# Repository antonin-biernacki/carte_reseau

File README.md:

# Carte réseau USB à base d'ATmega

Carte réseau USB conçue sous **KiCad**, construite autour d'un **ATmega**. Elle se présente comme une interface Ethernet (classe **RNDIS**, via la bibliothèque LUFA) et doit permettre à une carte mère de lire, écrire et lister des fichiers sur un PC, grâce à un protocole maison transporté en UDP : le **ProtocolAntique**. Un serveur C côté PC traite les requêtes.

> **État du projet** : ce dépôt est un état d'avancement. Le projet n'a pas été mené à son terme, voir [Avancement](#avancement).

## Sommaire

- [Contexte](#contexte)
- [Avancement](#avancement)
- [Aperçu](#aperçu)
- [Fonctionnalités](#fonctionnalités)
- [Structure du projet](#structure-du-projet)
- [Matériel](#matériel)
- [Compilation et téléversement](#compilation-et-téléversement)
- [Utilisation](#utilisation)
- [Fonctionnement interne](#fonctionnement-interne)
- [Crédits](#crédits)

## Contexte

L'idée est la suivante :

1. la carte mère exprime un besoin (`ls`, `read`, `write`) à la carte réseau ;
2. la carte réseau encapsule ce besoin dans une requête UDP (ProtocolAntique) et l'envoie au PC par l'USB ;
3. un serveur tourne sur le PC, exécute l'opération sur son système de fichiers et répond.

## Avancement

| Élément                                                             | État      |
|---------------------------------------------------------------------|-----------|
| Schématique et routage de la carte, soudage                         | Terminé   |
| Programmation de la carte et pilotage des LEDs                      | Terminé   |
| Reconnaissance de la carte comme interface réseau USB (RNDIS), `ping` | Terminé   |
| Réception de trames Ethernet et de paquets UDP (signalée par LED)   | Terminé   |
| Envoi d'une trame UDP depuis la carte (capturée avec Wireshark)     | Terminé   |
| Spécification du ProtocolAntique                                    | Terminé   |
| Serveur PC (`ls`, `read`, `write`) et ses outils de test            | Terminé et testé |
| Traitement des requêtes ProtocolAntique par la carte                | À faire   |
| Liaison avec la carte mère (shield), par SPI                        | À faire   |

Faute de temps, la carte n'a pas été reliée à la carte mère. La communication SPI a toutefois été validée lors du développement de l'ordonnanceur.

## Aperçu

### Schématique

### Routage

## Fonctionnalités

- Énumération USB de la carte comme interface Ethernet (RNDIS)
- Réception et traitement de trames Ethernet, avec indication par LED
- Envoi d'une trame UDP de test contenant une requête ProtocolAntique
- Protocole applicatif maison (ProtocolAntique) à trois opérations : `LS`, `READ`, `WRITE`
- Serveur PC UDP qui exécute ces opérations sur le système de fichiers
- Outils de simulation pour tester le serveur sans la carte (client de requêtes et faux récepteur)

## Structure du projet

```text
.
├── docs/                              # Captures et vidéos de démonstration
├── hardware/                          # Projet KiCad de la carte réseau
└── software/
    ├── CReseau/
    │   ├── test.c                     # Test autonome des LEDs de la carte
    │   └── Makefile
    ├── lufa-LUFA-210130-NSI/
    │   └── PicoCReseau/RNDISEthernet/ # Firmware de la carte (basé sur la démo RNDIS de LUFA)
    │       ├── RNDISEthernet.c        # main, tâches USB/RNDIS, envoi de la trame de test
    │       ├── Config/AppConfig.h     # Adresses IP et MAC
    │       ├── Lib/UDP.c              # Aiguillage des paquets UDP par port
    │       ├── Lib/ProtocolAntique.c  # Traitement du ProtocolAntique
    │       ├── Lib/ProtocolAntique.h  # En-tête et codes d'opération
    │       └── makefile
    └── serveurProtocolAntique/
        ├── serveur/                   # Serveur PC (reçoit et traite les requêtes)
        ├── testUDP/                   # Outils de simulation (client et faux récepteur)
        ├── descriptionProtocol.txt    # Description du ProtocolAntique
        ├── fonctionnement.txt         # Mode d'emploi du serveur et des tests
        └── Makefile
```

Le dossier `software/testUDP/` est une version antérieure des outils de test, conservée telle quelle.

## Matériel

La carte est construite autour d'un **ATmega** (USB natif, horloge à 16 MHz) et comprend :

- 5 LEDs d'état de communication, une LED d'alimentation et une LED de connexion ISP
- un **MAX232** avec des connecteurs **DB9** et **DB25**, pour utiliser la carte sur un terminal série
- un connecteur 6x1 qui expose les broches `PF` inutilisées, pour réutiliser la carte dans d'autres projets
- un connecteur USB, par lequel elle se présente au PC

Affectation des broches utilisées par le logiciel :

| Élément          | Broche |
|------------------|--------|
| LED 1            | PD0    |
| LED 2            | PD1    |
| LED 3            | PD6    |
| LED 4            | PD5    |
| LED 5            | PD4    |
| Ligne CS (test)  | PB5    |

Rôle des LEDs dans le firmware :

| LED                | Signification                                              |
|--------------------|------------------------------------------------------------|
| LED 1              | Allumée pendant le traitement d'une trame Ethernet reçue   |
| LED 4 et LED 5     | Allumées à la réception d'un paquet UDP sur le port 3333   |

Les LEDs sont éteintes à la fin du traitement de chaque trame.

## Compilation et téléversement

Les outils nécessaires sont `avr-gcc`, `make`, `dfu-programmer` (carte) et `gcc` (serveur).

### Firmware de la carte

Depuis `software/lufa-LUFA-210130-NSI/PicoCReseau/RNDISEthernet/` :

```bash
make          # produit RNDISEthernet.hex
make dfu      # téléverse sur la carte (ATmega en mode DFU)
make clean
```

### Test des LEDs

Depuis `software/CReseau/` :

```bash
make          # produit test.hex
make flash    # téléverse en DFU
make clean
```

### Serveur PC et outils de test

Depuis `software/serveurProtocolAntique/` :

```bash
make          # compile serveur, testUDP et serveur_carte
make clean
```

## Utilisation

### Avec la carte

Branchez la carte en USB, puis configurez l'interface réseau qu'elle crée (`eth2` dans notre cas, vérifiez son nom avec `ip link`) :

```bash
sudo ip link set eth2 up
sudo ip address add 10.0.0.1/24 dev eth2
ping 10.0.0.2
```

La carte a l'adresse `10.0.0.2` ; la configuration des adresses IP et MAC se trouve dans `Config/AppConfig.h`. Les paquets échangés peuvent être observés avec Wireshark sur l'interface de la carte.

### Serveur PC

Lancez le serveur depuis `software/serveurProtocolAntique/` :

```bash
./serveur/serveur
```

Il écoute en UDP sur le port **4242** et traite chaque requête reçue.

### Test du serveur sans la carte

Les requêtes de la carte sont simulées en loopback, dans trois terminaux :

```bash
./serveur/serveur                      # 1. le serveur (port 4242)
./testUDP/serveur_carte                # 2. faux récepteur qui joue la carte (port 5000)
./testUDP/testUDP ls <chemin>          # 3. requêtes simulées
./testUDP/testUDP read <chemin/fichier>
./testUDP/testUDP write <chemin/fichier> <ligne 1> ... <ligne n>
```

Sans chemin, `ls` liste le dossier depuis lequel le serveur a été lancé. Les fichiers créés avec `write` ne sont pas supprimés par `make clean` : à supprimer à la main.

Exemple de session de test : un `ls` (8 entrées, soit 9 réponses avec le message de fin), un `write` de 3 lignes dans `test.txt` (1 réponse de fin d'écriture) puis un `read` de ce fichier (5 lignes, soit 6 réponses avec le message de fin).

## Fonctionnement interne

### Côté carte

- **Interface réseau USB** : le firmware est la démo RNDIS de LUFA. La carte apparaît comme une carte Ethernet, les trames reçues sont placées dans un tampon (`FrameIN`) et celles à émettre dans un autre (`FrameOUT`).
- **Boucle principale** : elle enchaîne `Ethernet_Task()` (traitement des trames reçues), l'envoi de la trame de test (`SendRawEthernetPacket()`), `RNDIS_Task()` et `USB_USBTask()`.
- **Trame de test** : `SendRawEthernetPacket()` copie dans `FrameOUT` une trame complète (en-têtes Ethernet, IP, UDP) qui contient une requête `LS` à destination du port 3333.
- **Aiguillage UDP** : `Lib/UDP.c` oriente les paquets selon leur port de destination. Le port **3333** est celui du ProtocolAntique (supérieur à 1023 pour ne pas exiger les droits root) et est transmis à `ProtocolAntique_ProcessProtocolAntiquePacket()`.

### ProtocolAntique

Chaque message UDP contient un en-tête de 3 octets suivi du contenu, pour 256 octets au maximum :

| Octet | Champ       | Rôle                                                                                      |
|-------|-------------|-------------------------------------------------------------------------------------------|
| 0     | `operation` | Type de message                                                                           |
| 1     | `longueur`  | Nombre d'octets du contenu (0 à 252)                                                      |
| 2     | `numero`    | 0 pour une requête ; dans une réponse fragmentée, numéro du paquet (0 = dernier paquet) |

Opérations :

| Code   | Sens             | Message                      | Contenu                                    |
|--------|------------------|------------------------------|--------------------------------------------|
| `0x01` | carte → serveur  | Requête `LS`                 | chemin du dossier (vide = dossier courant) |
| `0x11` | serveur → carte  | Réponse `LS`                 | un nom d'entrée par message                |
| `0x02` | carte → serveur  | Requête `READ`               | chemin/nom du fichier                      |
| `0x12` | serveur → carte  | Réponse `READ`               | une ligne du fichier par message           |
| `0x03` | carte → serveur  | `WRITE` (début)              | chemin/nom du fichier                      |
| `0x13` | carte → serveur  | `WRITE` (données et fin)     | une ligne à écrire ; `numero` 0 = fin      |
| `0x23` | serveur → carte  | Réponse `WRITE`              | `0x00` si tout s'est bien passé, `0x01` si une erreur est survenue |

Une réponse fragmentée se termine toujours par un message de longueur 0 et de numéro 0.

### Côté serveur

- **Boucle de réception** : `boucleServeurUDP()` reçoit chaque message sur le port 4242 et le passe à `traitementMessageUDP()`. Les messages dont la longueur ne correspond pas à l'en-tête sont rejetés.
- **`LS`** : ouvre le dossier avec `opendir`, puis envoie un message de réponse par entrée (`readdir`), suivi du message de fin.
- **`READ`** : ouvre le fichier avec `fopen`, envoie une réponse par ligne (`fgets`), puis le message de fin si la lecture est allée jusqu'au bout.
- **`WRITE`** : mémorise le chemin reçu dans le message de début, puis ajoute chaque ligne au fichier. Le serveur vérifie que les numéros se suivent pour détecter un paquet perdu. Le message de fin déclenche la réponse `0x23`, avec un code de réussite ou d'erreur.
- **Réponses** : elles sont envoyées par `messageUDP()` à `IP_LOOPBACK` sur le port `PORT_CARTE` (5000), ce qui correspond au mode simulation. Pour répondre à la vraie carte, ces constantes sont à adapter dans `serveur.h` (`IP_CARTE` vaut `10.0.0.2`).

## Crédits

- Thomas Delobelle

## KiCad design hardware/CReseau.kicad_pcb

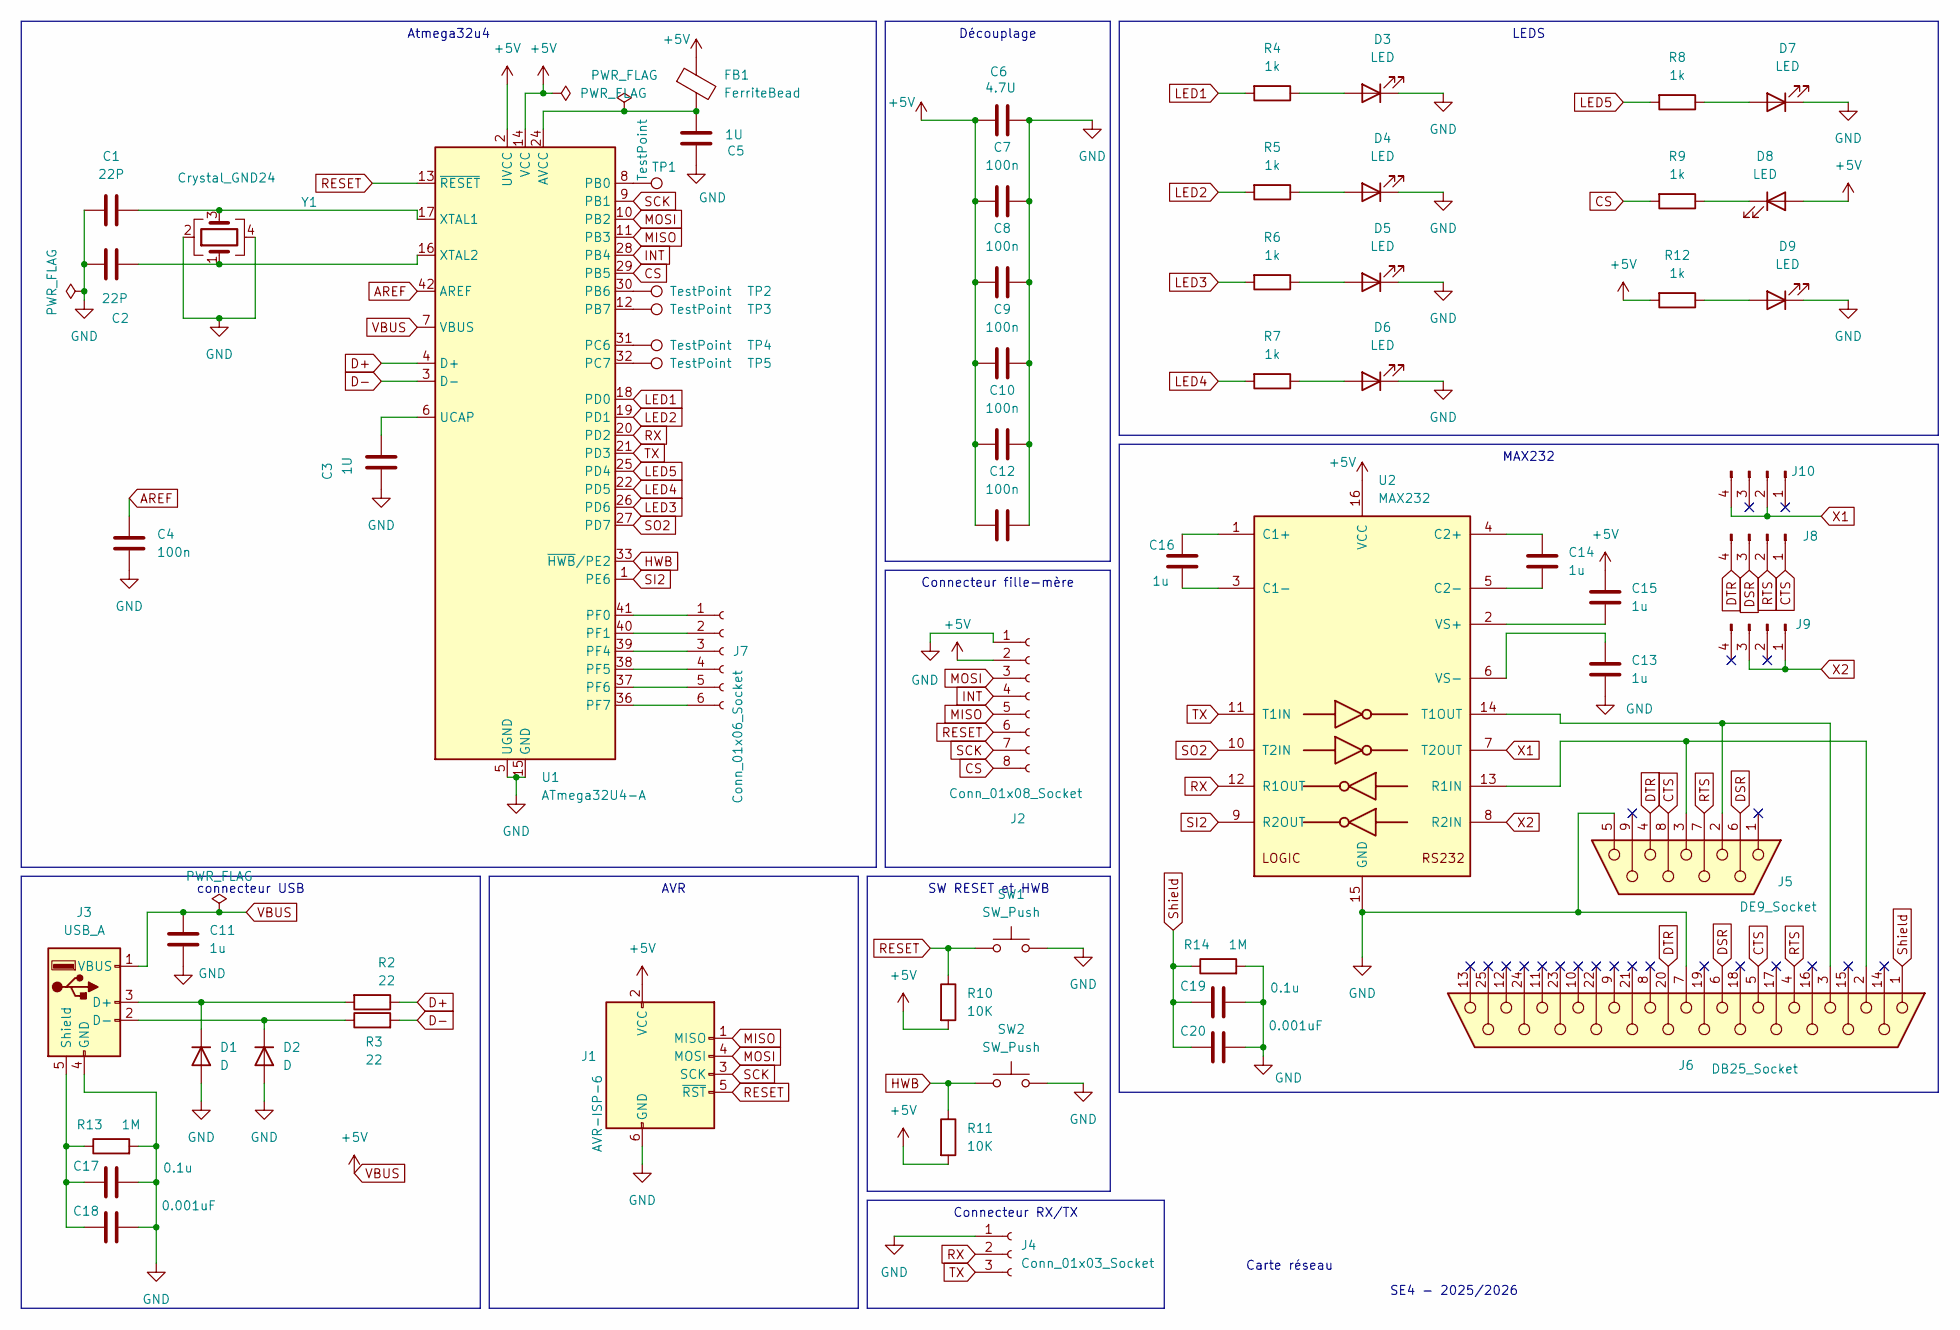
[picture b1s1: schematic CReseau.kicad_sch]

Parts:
C1, C2: 22P; C_0603_1608Metric_Pad1.08x0.95mm_HandSolder
C3, C5: 1U; C_0603_1608Metric_Pad1.08x0.95mm_HandSolder
C4, C7, C8, C9, C10, C12: 100n; C_0603_1608Metric_Pad1.08x0.95mm_HandSolder
C6: 4.7U; C_0603_1608Metric_Pad1.08x0.95mm_HandSolder
C11, C13, C14, C15, C16: 1u; C_0603_1608Metric_Pad1.08x0.95mm_HandSolder
C17, C19: 0.1u; C_0603_1608Metric_Pad1.08x0.95mm_HandSolder
C18, C20: 0.001uF; C_0603_1608Metric_Pad1.08x0.95mm_HandSolder
D1, D2: D; D_0603_1608Metric_Pad1.05x0.95mm_HandSolder
D3, D4, D5, D6, D7, D8, D9: LED; LED_0603_1608Metric_Pad1.05x0.95mm_HandSolder
FB1: FerriteBead; L_0805_2012Metric_Pad1.05x1.20mm_HandSolder
J1: AVR-ISP-6; PinHeader_2x03_P2.54mm_Vertical
J2: Conn_01x08_Socket; PinSocket_1x08_P2.54mm_Vertical
J3: USB_A; USB_A_CNCTech_1001-011-01101_Horizontal
J4: Conn_01x03_Socket; PinSocket_1x03_P2.54mm_Vertical
J5: DE9_Socket; DSUB-9_Pins_Horizontal_P2.77x2.54mm_EdgePinOffset9.40mm
J6: DB25_Socket; DSUB-25_Socket_Horizontal_P2.77x2.54mm_EdgePinOffset9.40mm
J7: Conn_01x06_Socket; PinSocket_1x06_P2.54mm_Vertical
J8, J9, J10: Conn_01x04_Pin; PinHeader_1x04_P2.54mm_Vertical
R2, R3: 22; R_0603_1608Metric_Pad0.98x0.95mm_HandSolder
R4, R5, R6, R7, R8, R9, R12: 1k; R_0603_1608Metric_Pad0.98x0.95mm_HandSolder
R10, R11: 10K; R_0603_1608Metric_Pad0.98x0.95mm_HandSolder
R13, R14: 1M; R_0603_1608Metric_Pad0.98x0.95mm_HandSolder
SW1, SW2: SW_Push; SW_Push_1P1T_NO_CK_KSC6xxJ
TP1, TP2, TP3, TP4, TP5: TestPoint; TestPoint_THTPad_D1.0mm_Drill0.5mm
U1: ATmega32U4-A; TQFP-44_10x10mm_P0.8mm
U2: MAX232; SOIC127P600X175-16N
Y1: Crystal_GND24; Crystal_SMD_SeikoEpson_FA238-4Pin_3.2x2.5mm_HandSoldering

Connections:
AREF: C4.2, U1.42 (AREF)
CS: J2.8, R9.2, U1.29 (PB5)
CTS: J5.8, J6.5, J8.1
D+: R2.1, U1.4 (D+)
D-: R3.2, U1.3 (D-)
DSR: J5.6, J6.6, J8.3
DTR: J5.4, J6.20, J8.4
GND: C1.1, C2.2, C3.1, C4.1, C5.1, C6.1, C7.2, C8.2, C9.2, C10.2, C11.1, C12.2, C13.1, C17.2, C18.2, C19.2, C20.2, D1.2 (A), D2.2 (A), D3.1 (K), D4.1 (K), D5.1 (K), D6.1 (K), D7.1 (K), D9.1 (K), J1.6 (GND), J2.1, J3.4 (GND), J4.1, J5.5, J6.7, R13.2, R14.2, SW1.2, SW2.2, U1.5 (UGND), U1.15 (GND), U1.23 (GND), U1.35 (GND), U1.43 (GND), U2.15 (GND), Y1.2, Y1.4
HWB: R11.1, SW2.1, U1.33 (~HWB/PE2)
INT: J2.4, U1.28 (PB4)
LED1: R4.2, U1.18 (PD0)
LED2: R5.2, U1.19 (PD1)
LED3: R6.2, U1.26 (PD6)
LED4: R7.2, U1.22 (PD5)
LED5: R8.2, U1.25 (PD4)
MISO: J1.1 (MISO), J2.5, U1.11 (PB3)
MOSI: J1.4 (MOSI), J2.3, U1.10 (PB2)
unnamed: C5.2, FB1.2, U1.24 (AVCC), U1.44 (AVCC)
unnamed: D1.1 (K), J3.3 (D+), R2.2
unnamed: D2.1 (K), J3.2 (D-), R3.1
unnamed: D3.2 (A), R4.1
unnamed: D4.2 (A), R5.1
unnamed: D5.2 (A), R6.1
unnamed: D6.2 (A), R7.1
unnamed: D7.2 (A), R8.1
unnamed: D8.1 (K), R9.1
unnamed: D9.2 (A), R12.1
unnamed: C17.1, C18.1, J3.5 (Shield), R13.1
unnamed: J7.1, U1.41 (PF0)
unnamed: J7.2, U1.40 (PF1)
unnamed: J7.3, U1.39 (PF4)
unnamed: J7.4, U1.38 (PF5)
unnamed: J7.5, U1.37 (PF6)
unnamed: J7.6, U1.36 (PF7)
unnamed: TP1.1, U1.8 (PB0)
unnamed: TP2.1, U1.30 (PB6)
unnamed: TP3.1, U1.12 (PB7)
unnamed: TP4.1, U1.31 (PC6)
unnamed: TP5.1, U1.32 (PC7)
unnamed: C3.2, U1.6 (UCAP)
unnamed: C1.2, U1.17 (XTAL1), Y1.3
unnamed: C2.1, U1.16 (XTAL2), Y1.1
unnamed: C16.2, U2.1 (C1+)
unnamed: C16.1, U2.3 (C1-)
unnamed: C14.2, U2.4 (C2+)
unnamed: C14.1, U2.5 (C2-)
unnamed: J5.3, J6.2, U2.13 (R1IN)
unnamed: J5.2, J6.3, U2.14 (T1OUT)
unnamed: C15.1, U2.2 (VS+)
unnamed: C13.2, U2.6 (VS-)
RESET: J1.5 (~RST), J2.6, R10.1, SW1.1, U1.13 (~RESET)
RTS: J5.7, J6.4, J8.2
RX: J4.2, U1.20 (PD2), U2.12 (R1OUT)
SCK: J1.3 (SCK), J2.7, U1.9 (PB1)
SI2: U1.1 (PE6), U2.9 (R2OUT)
SO2: U1.27 (PD7), U2.10 (T2IN)
Shield: C19.1, C20.1, J6.1, R14.1
TX: J4.3, U1.21 (PD3), U2.11 (T1IN)
VBUS: C6.2, C7.1, C8.1, C9.1, C10.1, C11.2, C12.1, C15.2, D8.2 (A), FB1.1, J1.2 (VCC), J2.2, J3.1 (VBUS), R10.2, R11.2, R12.2, U1.2 (UVCC), U1.7 (VBUS), U1.14 (VCC), U1.34 (VCC), U2.16 (VCC)
X1: J10.2, J10.4, U2.7 (T2OUT)
X2: J9.1, J9.3, U2.8 (R2IN)

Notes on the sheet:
SE4 - 2025/2026
Carte réseau
Connecteur RX/TX
SW RESET et HWB
MAX232
LEDS
Découplage
Connecteur fille-mère
connecteur USB
AVR
Atmega32u4

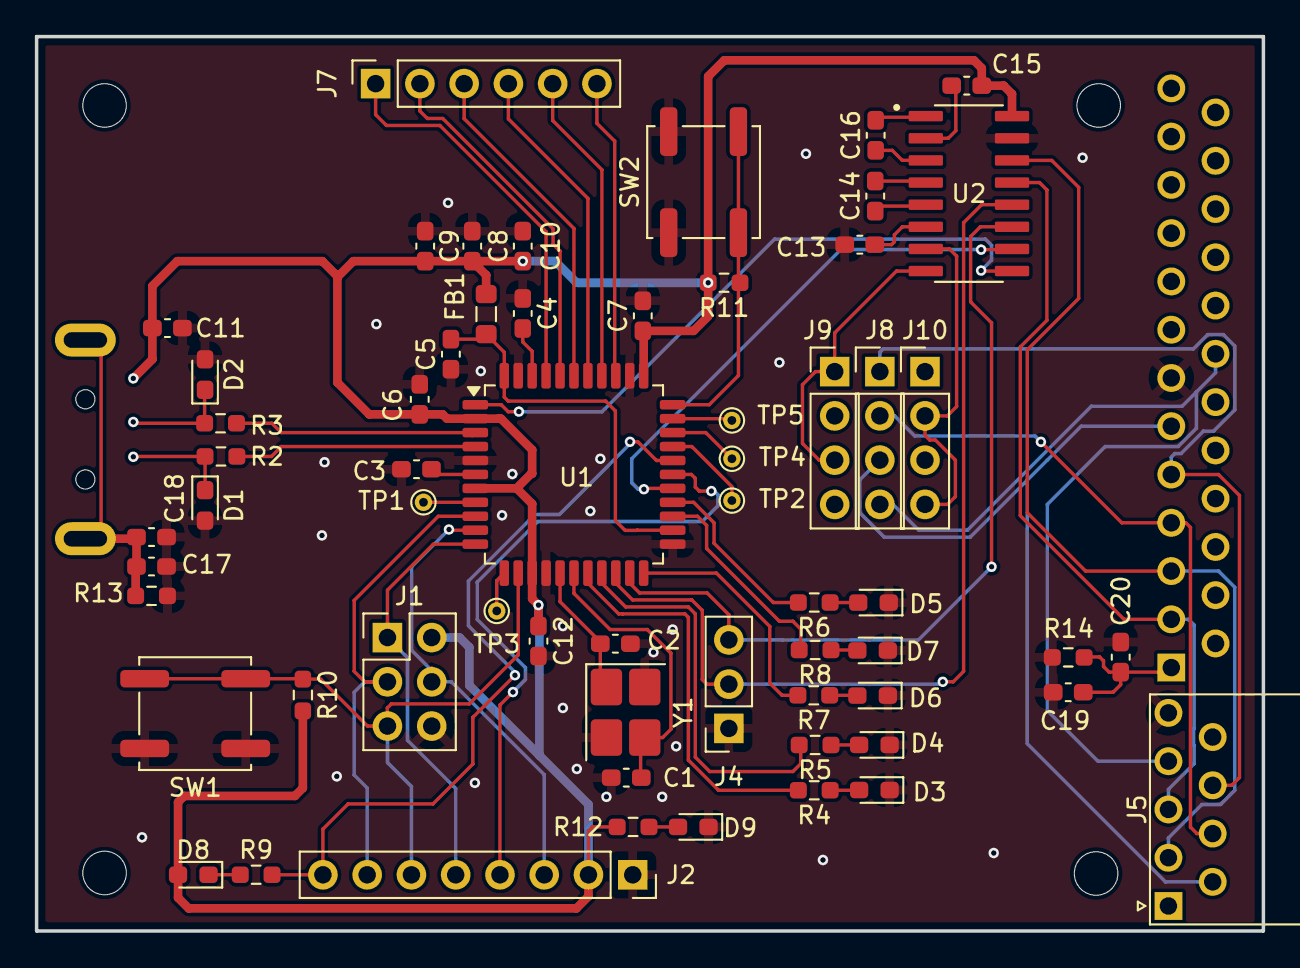
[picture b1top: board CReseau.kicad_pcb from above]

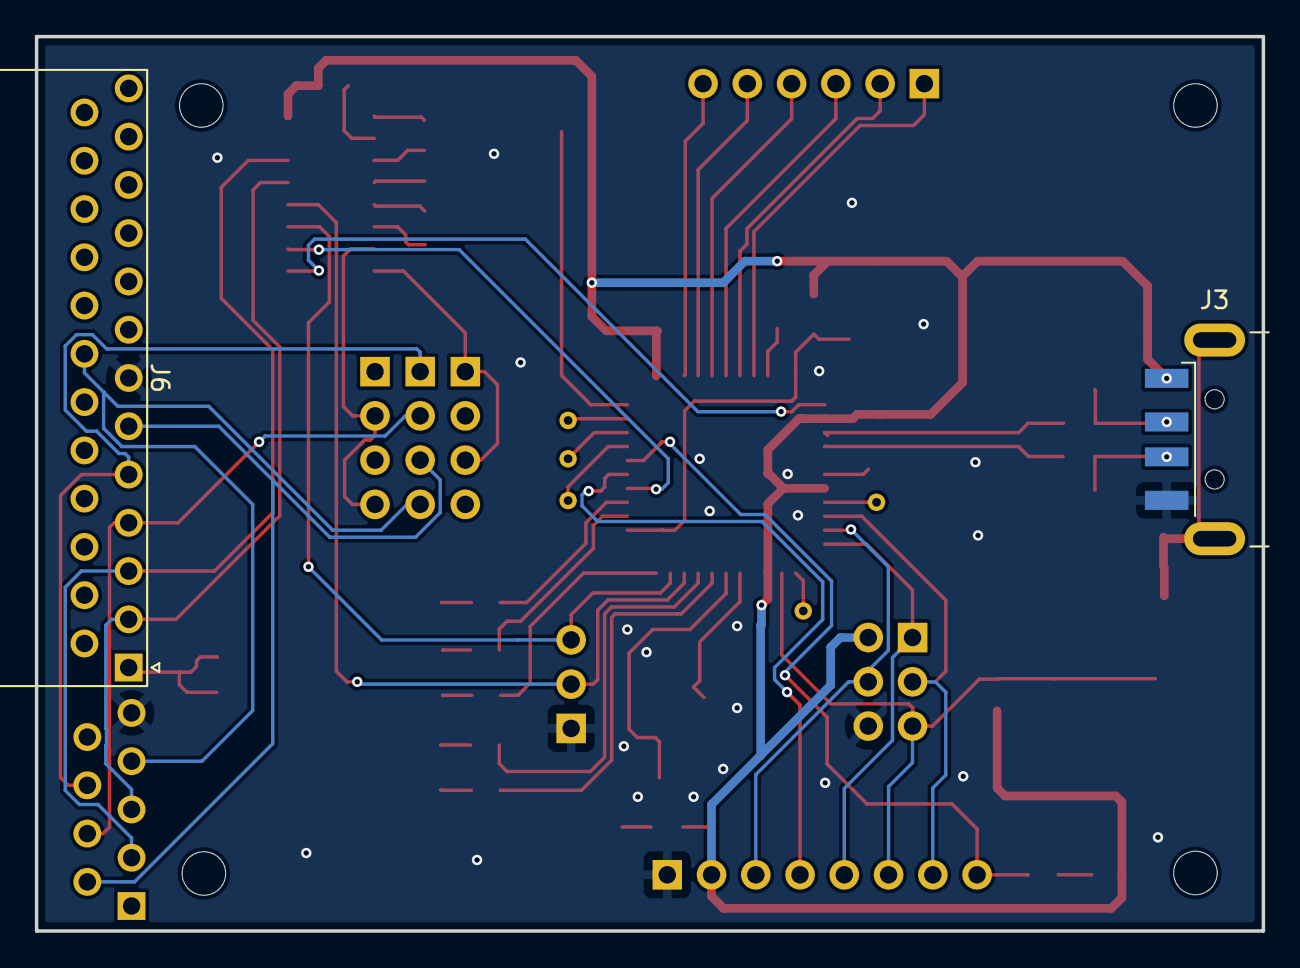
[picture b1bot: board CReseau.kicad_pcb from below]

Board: 2 copper layers, 70.4 x 51.3 mm, 63 parts (2 on the bottom side), 61 nets.

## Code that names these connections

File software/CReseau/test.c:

// avr-gcc -mmcu=atmega32u4 -Wall -Werror -I. -DF_CPU=16000000 -Os -o test.elf test.c
// avr-objcopy -j .text -j .data -O ihex test.elf test.hex


// Include
 
#include <stdint.h>
#include <stdlib.h>
#include <avr/io.h>
#include <util/delay.h>
#include <avr/interrupt.h>
 
// Define
 
#define LED1 0
#define LED2 1
#define LED3 6
#define LED4 5
#define LED5 4
#define CS 5




void led_init() {
    DDRD |= (1<<LED1);
	DDRD |= (1<< LED2);
	DDRD |= (1<< LED3);
	DDRD |= (1<< LED4);
	DDRD |= (1<< LED5);
	DDRB |= (1<< CS);

}


void leds_blink() {
	PORTD ^= (1<<LED1);
	PORTD ^= (1<<LED2);
	PORTD ^= (1<<LED3);
	PORTD ^= (1<<LED4);
	PORTD ^= (1<<LED5);
    PORTB ^= (1<<CS);
    
	_delay_ms(500);
}



int main() {
    led_init();
    while(1) {
        leds_blink();
    }
	return 0;
}
